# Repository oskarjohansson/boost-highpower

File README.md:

# Boost highpower
> Created by Oskar Johansson

**This is a synchronous boost module when the cheap 2A boost don't have the capacity to deliver enough powaer.**   

## Goals 
> Goals of this project
```
- Create a boost converter for at least 10A 
- Handle 5 - 40 V input 
- Handle 5 - 60 V output
```

## Directories 
```
Boost highpower
├── document        # Generic document folder
│   ├── datasheet   # Datasheet for hardware components  
├── hardware        
│   ├── pcb         # Schematic, layout and production files
│   │   └── gerber  # Production files
│   │   └── library # Library for project
└── img        # Thermal tests 
  ```

## Hardware 
> The hardware is pretty much the same used in Robot-SM project [RobotSM20-linefollower](https://github.com/caselabbet/robotsm20-linefollower) with following changes 
```
- Input capacitor to handle 5 - 35 V 
- Output capacitor to handle 5 - 55 V
- Potentiometer to control output
- Terminal blocks for wire
- Wide solderpads to solder wire 
```
The boost is consisting of a TPS43061, which is a *synchronous boost controller*, i.e. uses two external transistors instead of one transistor and a diode. This minimizes the losses in the diode that would have been about 5 - 7 W at 10A. 

When using the provided trimpot together with the resistors there is a hardware limit that unables to go beyond 55 V to output. Since the feedback reference is 1.22 V, you can find two resistors together with a trimpot to hold a certain intervall, as in the Matlab below.
```matlab
% Vfeedback is 1.22V 
syms Rsl Rsh
Rtrim = 10000;    
Vouth = 55;
Voutl = 5; 
eq1 = Voutl == 1.22*((Rsh)/(Rsl+Rtrim)+1);
eq2 = Vouth == 1.22*((Rsh+Rtrim)/(Rsl)+1);
solution = solve([eq1,eq2]);
Rsl = double(solution.Rsl);
Rsh = double(solution.Rsh);
Rshl_disp = sprintf('Resistor feedback with 10k trimpot, Rsl: %d Ohm, Rsh: %d Ohm \nGives a Vout of 5 to 55 V',Rsl,Rsh);
disp(Rshl_disp)
```
### Schematic 

### Rendered images

### BOM 
| Device              | Mfr nbr           | Quantity  | Value       |
| :---                | :---              | ---:      | ---:        |
| Boost controller    | TPS43061          | 1         | -           |
| Terminal block      | 1935161           | 2         | -           |
| Power inductor      | SRP1238A-R82M     | 1         | 0.82 µH     |
| Potentiometer       | 67PR10KLF         | 1         | 10k         |
| N-Mosfet            | CSD19502Q5BT      | 2         | 80V100A     | 
| Current resistor    | R2512W            | 1         | R002        |
| Electrolytic cap    | VZH-101M1KTR-1010 | 2         | 100 µF      |
| Electrolytic cap    | 865080653016      | 2         | 100 µF      |
| Resistor            | SMD 0603          | 5         | 2x 10R, 1k, 31.4k, 75k              |
| Capacitor           | SMD 0603          | 6         | 100 pF, 110 pF, 1.5 nF, 0.1 µF, 1µF |
| Capacitor           | SMD 0805          | 6         | 2x 0.1 µF, 4x 22µF                  |

## Usage of the boost module 
```
- Connect inputside to 4.5 - 35 V. 
- Control with an multimeter the output.
- Connect the output.
```

## License
> This project is created with MIT license.

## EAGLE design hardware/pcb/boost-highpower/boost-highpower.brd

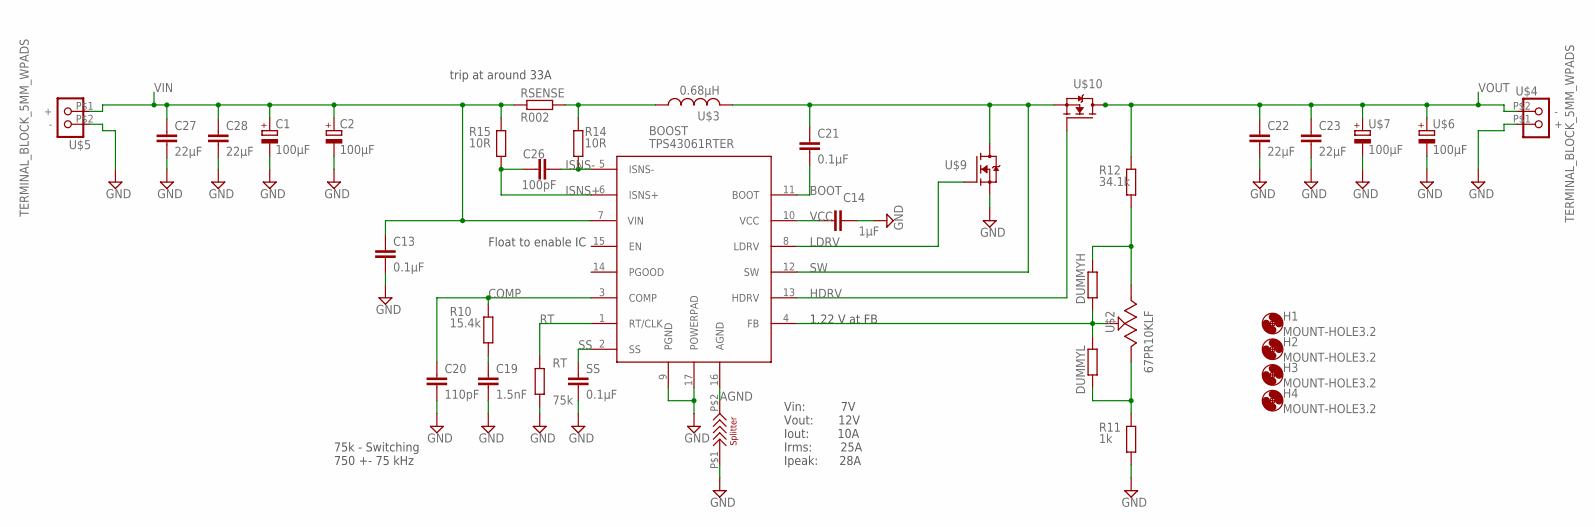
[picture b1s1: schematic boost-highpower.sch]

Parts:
BOOST: TPS43061RTER; QFN50P300X300X80-17N
C1, C2: 100µF; CAPAE830X850N
C13, C21: 0.1µF; C0805
C14: 1µF; C0603
C19: 1.5nF; C0603
C20: 110pF; C0603
C22, C23, C27, C28: 22µF; C0805
C26: 100pF; C0603
DUMMYH: R-EU_R0201; R0201
DUMMYL: R-EU_R0201; R0201
H1, H2, H3, H4: MOUNT-HOLE3.2; 3,2
R10: 15.4k; R0603
R11: 1k; R0603
R12: 34.1k; R0603
R14, R15: 10R; R0603
RSENSE: R002; R2512W
RT: 75k; R0603
SS: 0.1µF; C0603
U$1: SPLITTER
U$2: 67PR10KLF
U$3: 0.68µH; INDM135125X330N
U$4, U$5: TERMINAL_BLOCK_5MM_WPADS; TERMINAL_5MM_WITH_SOLDERPADS
U$6, U$7: 100µF; CAPAE1030X1000N
U$9, U$10: CSD17301Q5A; Q5A

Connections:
AGND: BOOST.16 (AGND), U$1.P$2 (2)
BOOT: BOOST.11 (BOOT), C21.2
COMP: BOOST.3 (COMP), C20.1, R10.2
GND: BOOST.9 (PGND), BOOST.17 (POWERPAD), C1.2 (-), C2.2 (-), C13.2, C14.2, C19.2, C20.2, C22.2, C23.2, C27.2, C28.2, R11.1, RT.1, SS.2, U$1.P$1 (1), U$4.P$1 (+), U$5.P$2 (-), U$6.2 (-), U$7.2 (-), U$9.1 (S), U$9.2 (S), U$9.3 (S)
HDRV: BOOST.13 (HDRV), U$10.4 (G)
ISNS+: BOOST.6 (ISNS+), C26.1, R15.1
ISNS-: BOOST.5 (ISNS-), C26.2, R14.1
LDRV: BOOST.8 (LDRV), U$9.4 (G)
unnamed: DUMMYH.2, R12.1, U$2.P$3 (3)
unnamed: DUMMYL.1, R11.2, U$2.P$1 (1)
unnamed: C19.1, R10.1
unnamed: R14.2, RSENSE.2, U$3.1
unnamed: BOOST.4 (FB), DUMMYH.1, DUMMYL.2, U$2.P$2 (2)
RT: BOOST.1 (RT/CLK), RT.2
SS: BOOST.2 (SS), SS.1
SW: BOOST.12 (SW), C21.1, U$3.2, U$9.5 (D), U$9.6 (D), U$9.7 (D), U$9.8 (D), U$9.9 (D), U$10.1 (S), U$10.2 (S), U$10.3 (S)
VCC: BOOST.10 (VCC), C14.1
VIN: BOOST.7 (VIN), C1.1 (+), C2.1 (+), C13.1, C27.1, C28.1, R15.2, RSENSE.1, U$5.P$1 (+)
VOUT: C22.1, C23.1, R12.2, U$4.P$2 (-), U$6.1 (+), U$7.1 (+), U$10.5 (D), U$10.6 (D), U$10.7 (D), U$10.8 (D), U$10.9 (D)

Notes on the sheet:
75k - Switching 750 +- 75 kHz
1.22 V at FB
trip at around 33A
Vin: 7V Vout: 12V Iout: 10A Irms: 25A Ipeak: 28A
Float to enable IC

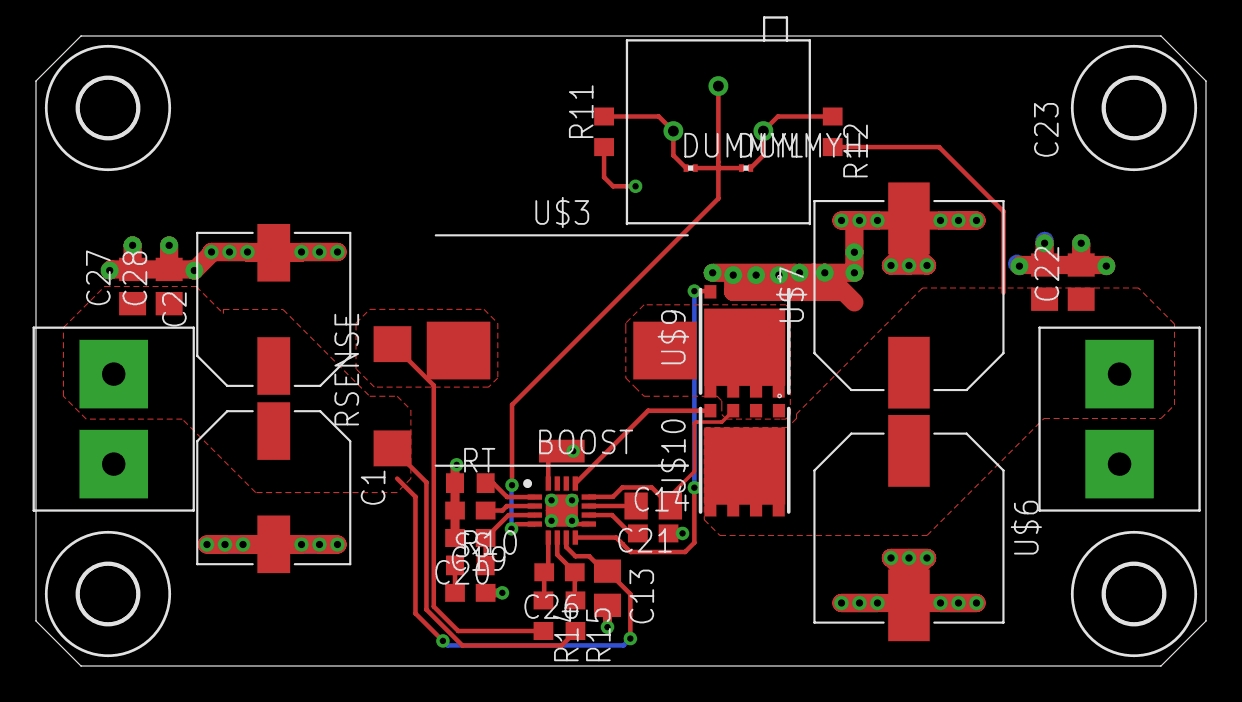
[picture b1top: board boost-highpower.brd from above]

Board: 2 copper layers, 65.0 x 35.0 mm, 36 parts (0 on the bottom side), 19 nets.

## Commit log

2020-03-25 Create hardware folder with lowercase
2020-03-25 Create project and copy boost from robotsm20-linefollower
2020-03-25 moved some components
2020-03-26 Moved components to a first place
2020-03-26 Routed board
2020-03-26 Rendered images
2020-03-29 Added 10A to silkscreen
2020-03-31 Changed cap to 50V and 100V to meet requirement
2020-04-01 Export schematic
2020-04-01 Removed bot, side and top view of render
2020-04-01 Render PCB
2020-04-01 Corrected typo in name of used controller
2020-04-01 Update README.md
    Added images, schematic, more information about the module
2020-04-02 Added BOM
